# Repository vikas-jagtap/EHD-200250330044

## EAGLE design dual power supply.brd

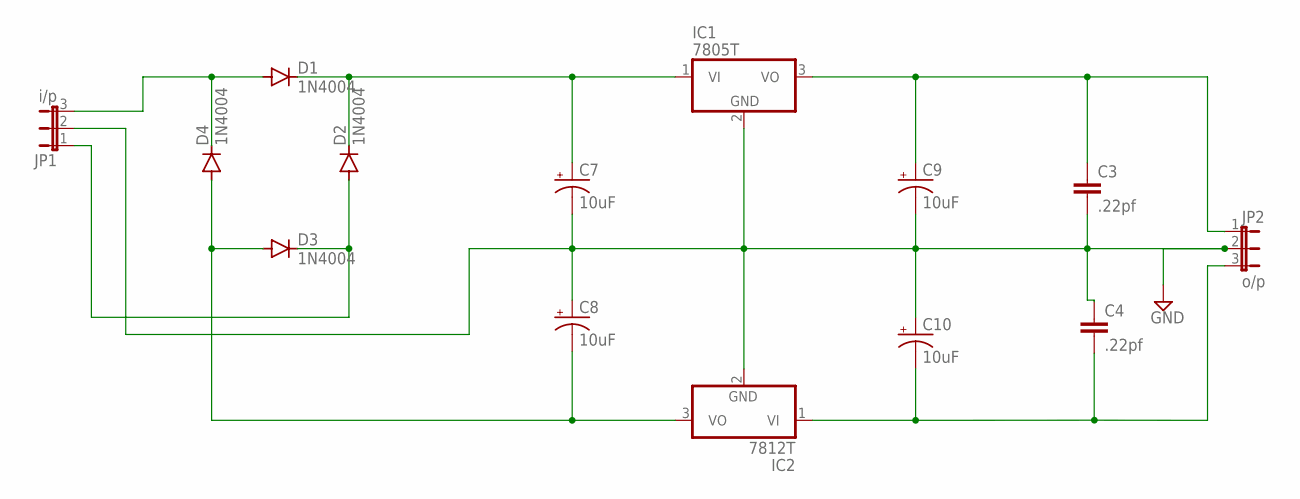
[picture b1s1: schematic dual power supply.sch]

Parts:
C3, C4: .22pf; C2.5-3
C7, C8, C9, C10: 10uF; E3,5-8
D1, D2, D3, D4: 1N4004; DO41-10
IC1: 7805T; TO220H
IC2: 7812T; TO220H
JP1: i/p; JP2
JP2: o/p; JP2

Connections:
GND: C3.2, C4.1, C7.-, C8.+, C9.-, C10.+, IC1.2 (GND), IC2.2 (GND), JP1.2, JP2.2
unnamed: D1.A, D4.C, JP1.3
unnamed: C7.+, D1.C, D2.C, IC1.1 (VI)
unnamed: C4.2, C10.-, IC2.1 (VI), JP2.3
unnamed: C3.1, C9.+, IC1.3 (VO), JP2.1
unnamed: D2.A, D3.C, JP1.1
unnamed: C8.-, D3.A, D4.A, IC2.3 (VO)

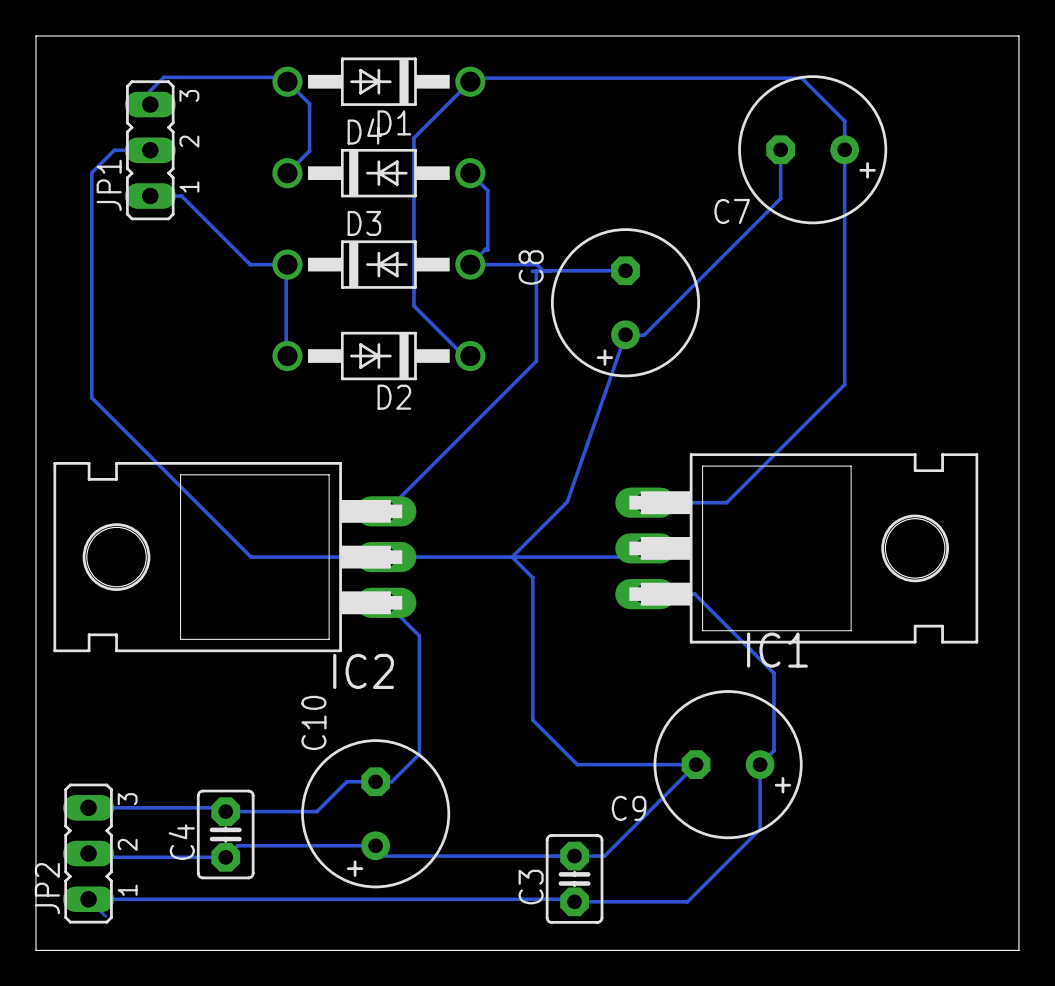
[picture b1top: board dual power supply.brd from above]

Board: 2 copper layers, 54.6 x 50.8 mm, 14 parts (0 on the bottom side), 7 nets.

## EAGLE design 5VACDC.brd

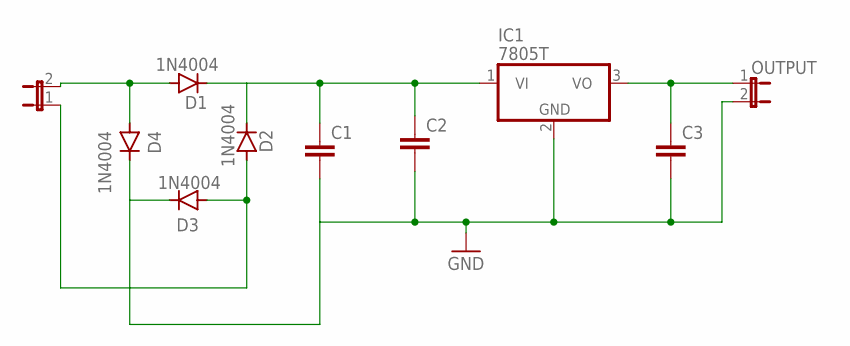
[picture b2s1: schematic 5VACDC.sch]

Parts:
C1, C2, C3: C2,5-3; C2.5-3
D1, D2, D3, D4: 1N4004; DO41-10
IC1: 7805T; TO220H
INPUT: JP1E; JP1
OUTPUT: JP1E; JP1

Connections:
GND: C1.2, C2.2, C3.2, D3.C, D4.C, IC1.2 (GND), OUTPUT.2
unnamed: D1.A, D4.A, INPUT.2
unnamed: C1.1, C2.1, D1.C, D2.C, IC1.1 (VI)
unnamed: D2.A, D3.A, INPUT.1
unnamed: C3.1, IC1.3 (VO), OUTPUT.1

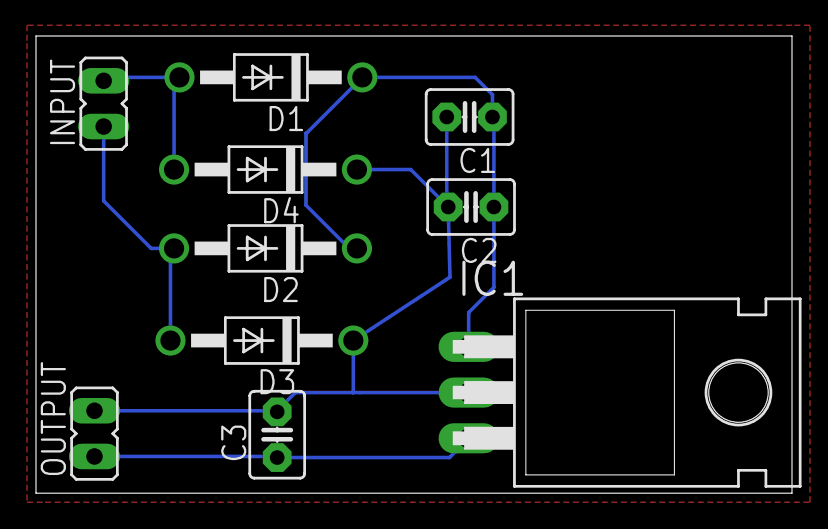
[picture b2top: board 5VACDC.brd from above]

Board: 2 copper layers, 42.0 x 25.4 mm, 10 parts (0 on the bottom side), 5 nets.

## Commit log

2020-10-01 Added New project
2021-02-03 Jay gajanan
2021-02-03 vikas
